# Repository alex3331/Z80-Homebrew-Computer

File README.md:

# Z80-Homebrew-Computer
Custom-built Z80 computer with video display, PS/2 keyboard, sound, and ROM monitor

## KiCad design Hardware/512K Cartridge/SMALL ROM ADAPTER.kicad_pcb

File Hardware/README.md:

Z80 computer hardware schematics and PCB designs.

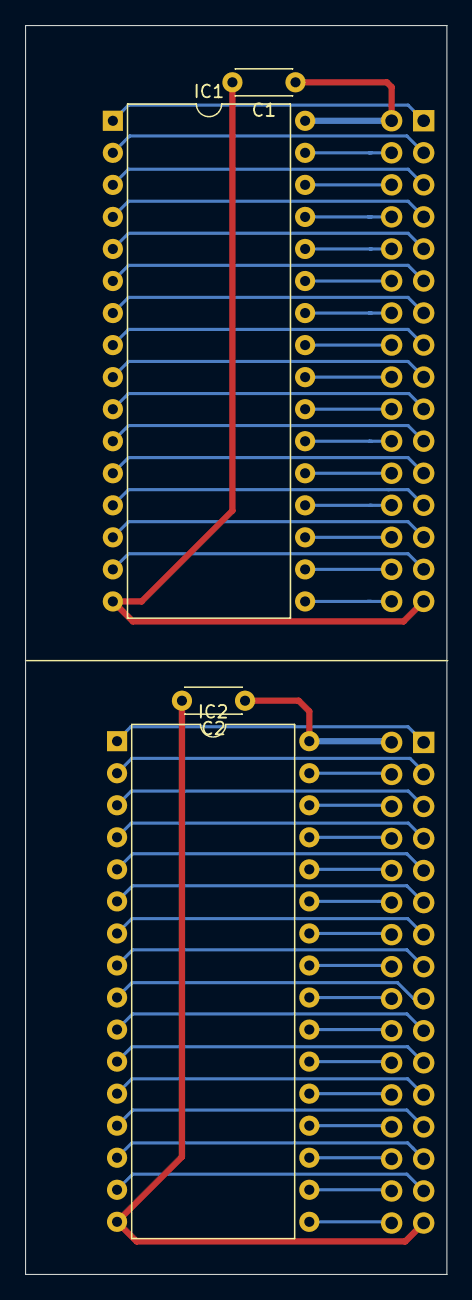
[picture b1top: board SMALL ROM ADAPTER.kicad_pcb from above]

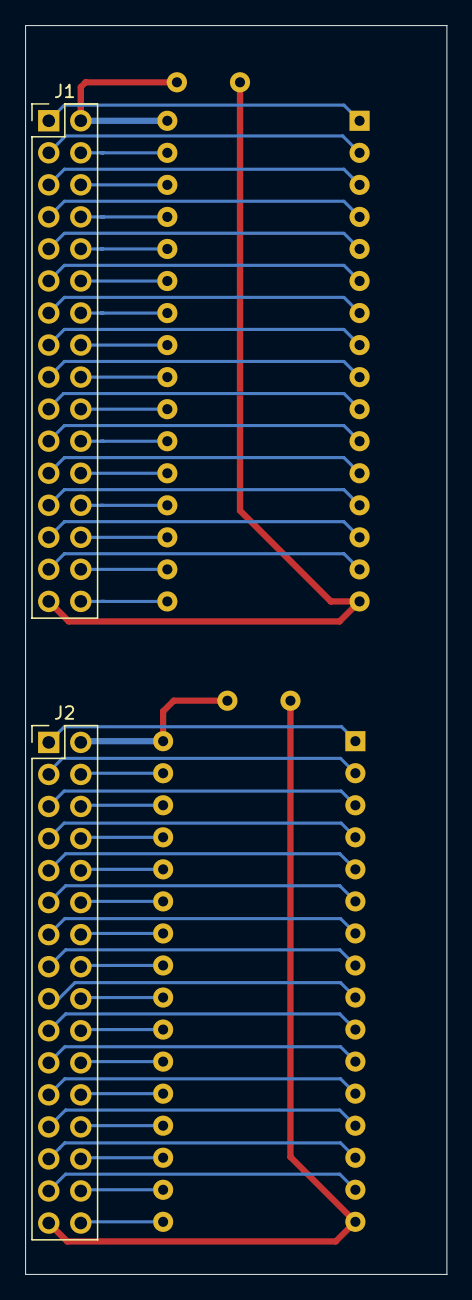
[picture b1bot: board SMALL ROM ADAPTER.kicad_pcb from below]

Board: 2 copper layers, 33.4 x 99.0 mm, 6 parts (2 on the bottom side), 64 nets.

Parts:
C1, C2: 0.1 uF; C_Disc_D4.3mm_W1.9mm_P5.00mm
IC1, IC2: SST39SF040-70-4C-PHE; DIP-32_W15.24mm
J1, J2: Conn_02x16_Odd_Even; PinHeader_2x16_P2.54mm_Vertical

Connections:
/1: IC1.1, J1.1
/1a: IC2.1, J2.1
/2: C1.1, IC1.32, J1.2
/2a: C2.1, IC2.32, J2.2
/3: IC1.2, J1.3
/3a: IC2.2, J2.3
/4: IC1.31, J1.4
/4a: IC2.31, J2.4
/5: IC1.3, J1.5
/5a: IC2.3, J2.5
/6: IC1.30, J1.6
/6a: IC2.30, J2.6
/7: IC1.4, J1.7
/7a: IC2.4, J2.7
/8: IC1.29, J1.8
/8a: IC2.29, J2.8
/9: IC1.5, J1.9
/9a: IC2.5, J2.9
/10: IC1.28, J1.10
/10a: IC2.28, J2.10
/11: IC1.6, J1.11
/11a: IC2.6, J2.11
/12: IC1.27, J1.12
/12a: IC2.27, J2.12
/13: IC1.7, J1.13
/13a: IC2.7, J2.13
/14: IC1.26, J1.14
/14a: IC2.26, J2.14
/15: IC1.8, J1.15
/15a: IC2.8, J2.15
/16: IC1.25, J1.16
/16a: IC2.25, J2.16
/17: IC1.9, J1.17
/17a: IC2.9, J2.17
/18: IC1.24, J1.18
/18a: IC2.24, J2.18
/19: IC1.10, J1.19
/19a: IC2.10, J2.19
/20: IC1.23, J1.20
/20a: IC2.23, J2.20
/21: IC1.11, J1.21
/21a: IC2.11, J2.21
/22: IC1.22, J1.22
/22a: IC2.22, J2.22
/23: IC1.12, J1.23
/23a: IC2.12, J2.23
/24: IC1.21, J1.24
/24a: IC2.21, J2.24
/25: IC1.13, J1.25
/25a: IC2.13, J2.25
/26: IC1.20, J1.26
/26a: IC2.20, J2.26
/27: IC1.14, J1.27
/27a: IC2.14, J2.27
/28: IC1.19, J1.28
/28a: IC2.19, J2.28
/29: IC1.15, J1.29
/29a: IC2.15, J2.29
/30: IC1.18, J1.30
/30a: IC2.18, J2.30
/31: C1.2, IC1.16, J1.31
/31a: C2.2, IC2.16, J2.31
/32: IC1.17, J1.32
/32a: IC2.17, J2.32

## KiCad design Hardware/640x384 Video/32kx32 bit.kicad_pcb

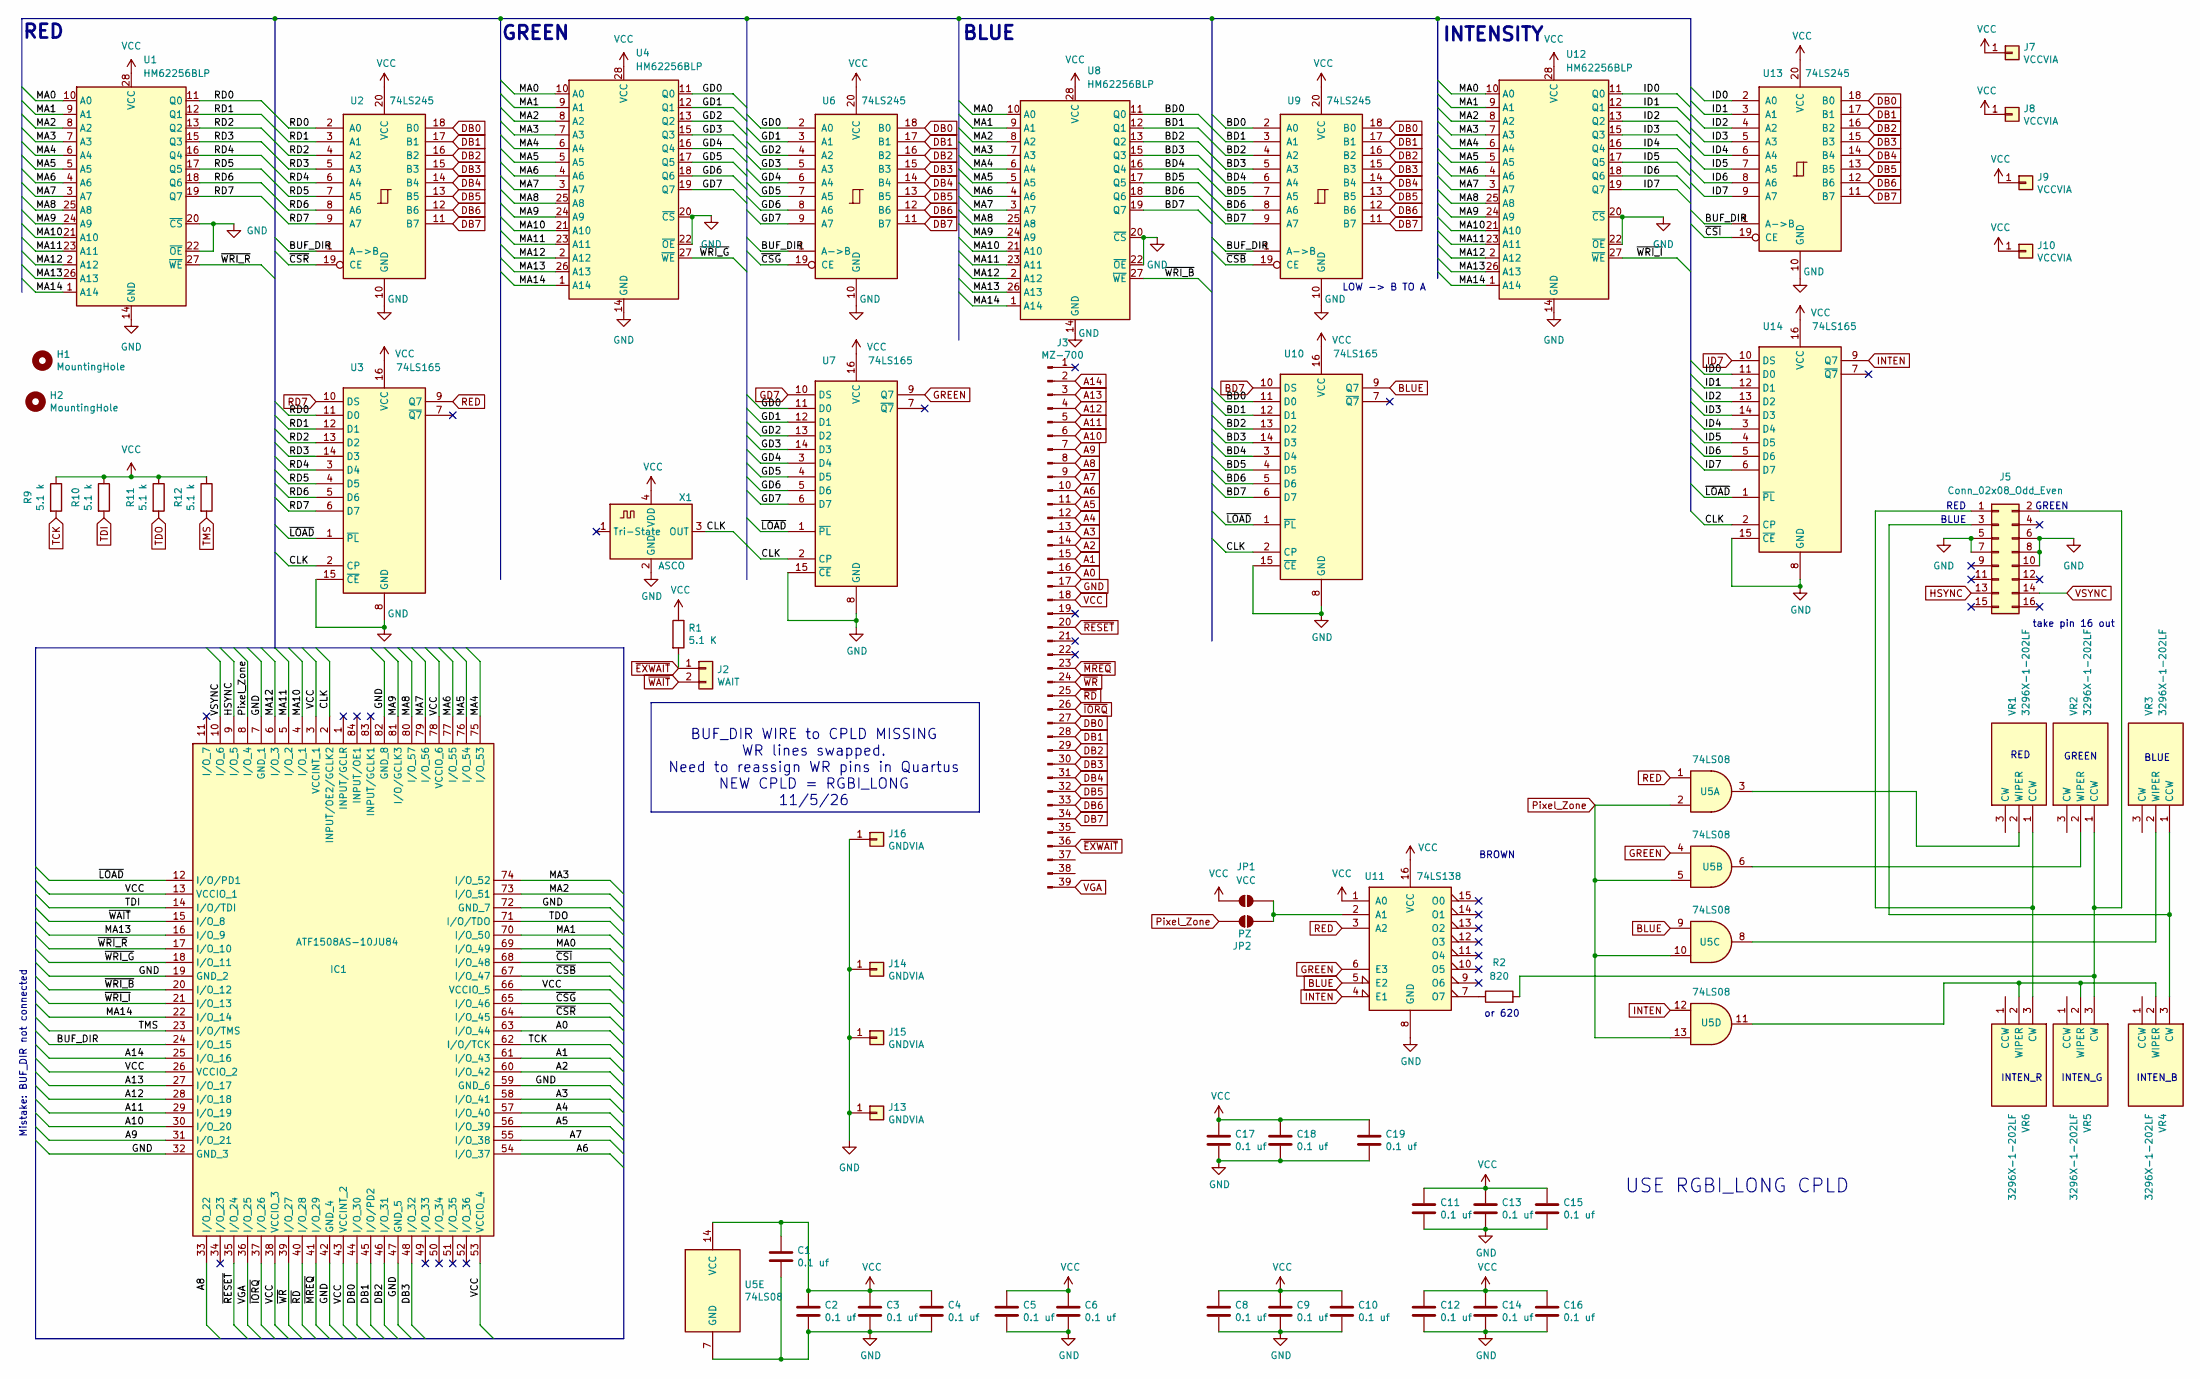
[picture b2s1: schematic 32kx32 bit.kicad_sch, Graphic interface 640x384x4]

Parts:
C1, C2, C3, C4, C5, C6, C8, C9, C10, C11, C12, C13, C14, C15, C16: 0.1 uf; C_Disc_D4.3mm_W1.9mm_P5.00mm
C17, C18, C19: 0.1 uf; C_Disc_D3.0mm_W2.0mm_P2.50mm
H1, H2: MountingHole; MountingHole_3.2mm_M3
IC1: ATF1508AS-10JU84; PLCC-84_THT-Socket; Manufacturer_Part_Number ATF1508AS-10JU84; Mouser Part Number 556-ATF1508AS-10JU84
J2: WAIT; PinHeader_1x02_P2.54mm_Vertical
J3: MZ-700; PinHeader_1x39_P2.54mm_Vertical
J5: Conn_02x08_Odd_Even; PinHeader_2x08_P2.54mm_Vertical
J7, J8, J9, J10: VCCVIA; PinHeader_1x01_P2.54mm_Vertical
J13, J14, J15, J16: GNDVIA; PinHeader_1x01_P2.54mm_Vertical
JP1: VCC; SolderJumper-2_P1.3mm_Open_RoundedPad1.0x1.5mm
JP2: PZ; SolderJumper-2_P1.3mm_Open_RoundedPad1.0x1.5mm
R1: 5.1 K; R_Axial_DIN0204_L3.6mm_D1.6mm_P5.08mm_Horizontal
R2: 820; R_Axial_DIN0204_L3.6mm_D1.6mm_P5.08mm_Horizontal
R9, R10, R11, R12: 5.1 k; R_Axial_DIN0204_L3.6mm_D1.6mm_P5.08mm_Horizontal
U1, U4, U8, U12: HM62256BLP; DIP-28_W7.62mm
U2, U6, U9, U13: 74LS245; DIP-20_W7.62mm
U3, U7, U10, U14: 74LS165; DIP-16_W7.62mm
U5: 74LS08; DIP-14_W7.62mm
U11: 74LS138; DIP-16_W7.62mm
VR1, VR2, VR3, VR4, VR5, VR6: 3296X-1-202LF; 3296X1202LF; Manufacturer_Part_Number 3296X-1-202LF; Mouser Part Number 652-3296X-1-202LF
X1: ASCO; Oscillator_DIP-8

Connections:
/BD0: U8.11 (Q0), U9.2 (A0), U10.11 (D0)
/BD1: U8.12 (Q1), U9.3 (A1), U10.12 (D1)
/BD2: U8.13 (Q2), U9.4 (A2), U10.13 (D2)
/BD3: U8.15 (Q3), U9.5 (A3), U10.14 (D3)
/BD4: U8.16 (Q4), U9.6 (A4), U10.3 (D4)
/BD5: U8.17 (Q5), U9.7 (A5), U10.4 (D5)
/BD6: U8.18 (Q6), U9.8 (A6), U10.5 (D6)
/BUF_DIR: IC1.24 (I/O_15), U2.1 (A->B), U6.1 (A->B), U9.1 (A->B), U13.1 (A->B)
/CLK: IC1.2 (INPUT/OE2/GCLK2), U3.2 (CP), U7.2 (CP), U10.2 (CP), U14.2 (CP), X1.3 (OUT)
/GD0: U4.11 (Q0), U6.2 (A0), U7.11 (D0)
/GD1: U4.12 (Q1), U6.3 (A1), U7.12 (D1)
/GD2: U4.13 (Q2), U6.4 (A2), U7.13 (D2)
/GD3: U4.15 (Q3), U6.5 (A3), U7.14 (D3)
/GD4: U4.16 (Q4), U6.6 (A4), U7.3 (D4)
/GD5: U4.17 (Q5), U6.7 (A5), U7.4 (D5)
/GD6: U4.18 (Q6), U6.8 (A6), U7.5 (D6)
/ID0: U12.11 (Q0), U13.2 (A0), U14.11 (D0)
/ID1: U12.12 (Q1), U13.3 (A1), U14.12 (D1)
/ID2: U12.13 (Q2), U13.4 (A2), U14.13 (D2)
/ID3: U12.15 (Q3), U13.5 (A3), U14.14 (D3)
/ID4: U12.16 (Q4), U13.6 (A4), U14.3 (D4)
/ID5: U12.17 (Q5), U13.7 (A5), U14.4 (D5)
/ID6: U12.18 (Q6), U13.8 (A6), U14.5 (D6)
/MA0: IC1.69 (I/O_49), U1.10 (A0), U4.10 (A0), U8.10 (A0), U12.10 (A0)
/MA1: IC1.70 (I/O_50), U1.9 (A1), U4.9 (A1), U8.9 (A1), U12.9 (A1)
/MA2: IC1.73 (I/O_51), U1.8 (A2), U4.8 (A2), U8.8 (A2), U12.8 (A2)
/MA3: IC1.74 (I/O_52), U1.7 (A3), U4.7 (A3), U8.7 (A3), U12.7 (A3)
/MA4: IC1.75 (I/O_53), U1.6 (A4), U4.6 (A4), U8.6 (A4), U12.6 (A4)
/MA5: IC1.76 (I/O_54), U1.5 (A5), U4.5 (A5), U8.5 (A5), U12.5 (A5)
/MA6: IC1.77 (I/O_55), U1.4 (A6), U4.4 (A6), U8.4 (A6), U12.4 (A6)
/MA7: IC1.79 (I/O_56), U1.3 (A7), U4.3 (A7), U8.3 (A7), U12.3 (A7)
/MA8: IC1.80 (I/O_57), U1.25 (A8), U4.25 (A8), U8.25 (A8), U12.25 (A8)
/MA9: IC1.81 (I/O/GCLK3), U1.24 (A9), U4.24 (A9), U8.24 (A9), U12.24 (A9)
/MA10: IC1.4 (I/O_1), U1.21 (A10), U4.21 (A10), U8.21 (A10), U12.21 (A10)
/MA11: IC1.5 (I/O_2), U1.23 (A11), U4.23 (A11), U8.23 (A11), U12.23 (A11)
/MA12: IC1.6 (I/O_3), U1.2 (A12), U4.2 (A12), U8.2 (A12), U12.2 (A12)
/MA13: IC1.16 (I/O_9), U1.26 (A13), U4.26 (A13), U8.26 (A13), U12.26 (A13)
/MA14: IC1.22 (I/O_14), U1.1 (A14), U4.1 (A14), U8.1 (A14), U12.1 (A14)
/RD0: U1.11 (Q0), U2.2 (A0), U3.11 (D0)
/RD1: U1.12 (Q1), U2.3 (A1), U3.12 (D1)
/RD2: U1.13 (Q2), U2.4 (A2), U3.13 (D2)
/RD3: U1.15 (Q3), U2.5 (A3), U3.14 (D3)
/RD4: U1.16 (Q4), U2.6 (A4), U3.3 (D4)
/RD5: U1.17 (Q5), U2.7 (A5), U3.4 (D5)
/RD6: U1.18 (Q6), U2.8 (A6), U3.5 (D6)
/~CSB: IC1.67 (I/O_47), U9.19 (CE)
/~CSG: IC1.65 (I/O_46), U6.19 (CE)
/~CSI: IC1.68 (I/O_48), U13.19 (CE)
/~CSR: IC1.64 (I/O_45), U2.19 (CE)
/~LOAD: IC1.12 (I/O/PD1), U3.1 (~PL), U7.1 (~PL), U10.1 (~PL), U14.1 (~PL)
/~WRI_B: IC1.20 (I/O_12), U8.27 (~WE)
/~WRI_G: IC1.18 (I/O_11), U4.27 (~WE)
/~WRI_I: IC1.21 (I/O_13), U12.27 (~WE)
/~WRI_R: IC1.17 (I/O_10), U1.27 (~WE)
A0: IC1.63 (I/O_44), J3.16
A1: IC1.61 (I/O_43), J3.15
A2: IC1.60 (I/O_42), J3.14
A3: IC1.58 (I/O_41), J3.13
A4: IC1.57 (I/O_40), J3.12
A5: IC1.56 (I/O_39), J3.11
A6: IC1.54 (I/O_37), J3.10
A7: IC1.55 (I/O_38), J3.9
A8: IC1.33 (I/O_22), J3.8
A9: IC1.31 (I/O_21), J3.7
A10: IC1.30 (I/O_20), J3.6
A11: IC1.29 (I/O_19), J3.5
A12: IC1.28 (I/O_18), J3.4
A13: IC1.27 (I/O_17), J3.3
A14: IC1.25 (I/O_16), J3.2
BD7: U8.19 (Q7), U9.9 (A7), U10.6 (D7), U10.10 (DS)
BLUE: U5.9, U10.9 (Q7), U11.5 (E2)
DB0: IC1.44 (I/O_30), J3.27, U2.18 (B0), U6.18 (B0), U9.18 (B0), U13.18 (B0)
DB1: IC1.45 (I/O/PD2), J3.28, U2.17 (B1), U6.17 (B1), U9.17 (B1), U13.17 (B1)
DB2: IC1.46 (I/O_31), J3.29, U2.16 (B2), U6.16 (B2), U9.16 (B2), U13.16 (B2)
DB3: IC1.48 (I/O_32), J3.30, U2.15 (B3), U6.15 (B3), U9.15 (B3), U13.15 (B3)
DB4: J3.31, U2.14 (B4), U6.14 (B4), U9.14 (B4), U13.14 (B4)
DB5: J3.32, U2.13 (B5), U6.13 (B5), U9.13 (B5), U13.13 (B5)
DB6: J3.33, U2.12 (B6), U6.12 (B6), U9.12 (B6), U13.12 (B6)
DB7: J3.34, U2.11 (B7), U6.11 (B7), U9.11 (B7), U13.11 (B7)
GD7: U4.19 (Q7), U6.9 (A7), U7.6 (D7), U7.10 (DS)
GND: C1.2, C2.2, C3.2, C4.2, C5.2, C6.2, C8.2, C9.2, C10.2, C11.2, C12.2, C13.2, C14.2, C15.2, C16.2, C17.2, C18.2, C19.2, IC1.7 (GND_1), IC1.19 (GND_2), IC1.32 (GND_3), IC1.42 (GND_4), IC1.47 (GND_5), IC1.59 (GND_6), IC1.72 (GND_7), IC1.82 (GND_8), J3.17, J5.5, J5.6, J5.7, J5.8, J5.10, J13.1 (Pin_1_1), J14.1 (Pin_1_1), J15.1 (Pin_1_1), J16.1 (Pin_1_1), U1.14 (GND), U1.20 (~CS), U1.22 (~OE), U2.10 (GND), U3.8 (GND), U3.15 (~CE), U4.14 (GND), U4.20 (~CS), U4.22 (~OE), U5.7 (GND), U6.10 (GND), U7.8 (GND), U7.15 (~CE), U8.14 (GND), U8.20 (~CS), U8.22 (~OE), U9.10 (GND), U10.8 (GND), U10.15 (~CE), U11.8 (GND), U12.14 (GND), U12.20 (~CS), U12.22 (~OE), U13.10 (GND), U14.8 (GND), U14.15 (~CE), X1.2 (GND)
GREEN: U5.4, U7.9 (Q7), U11.6 (E3)
HSYNC: IC1.9 (I/O_5), J5.13
ID7: U12.19 (Q7), U13.9 (A7), U14.6 (D7), U14.10 (DS)
INTEN: U5.12, U11.4 (E1), U14.9 (Q7)
unnamed: J5.1, VR1.1 (CCW), VR6.3 (CW)
unnamed: J5.2, R2.2, VR2.1 (CCW), VR5.3 (CW)
unnamed: J5.3, VR3.1 (CCW), VR4.3 (CW)
unnamed: JP1.2 (B), JP2.2 (B), U11.2 (A1)
unnamed: R2.1, U11.7 (O7)
unnamed: U5.3, VR1.2 (WIPER)
unnamed: U5.6, VR2.2 (WIPER)
unnamed: U5.8, VR3.2 (WIPER)
unnamed: U5.11, VR4.2 (WIPER), VR5.2 (WIPER), VR6.2 (WIPER)
Pixel_Zone: IC1.8 (I/O_4), JP2.1 (A), U5.2, U5.5, U5.10, U5.13
RD7: U1.19 (Q7), U2.9 (A7), U3.6 (D7), U3.10 (DS)
RED: U3.9 (Q7), U5.1, U11.3 (A2)
TCK: IC1.62 (I/O/TCK), R9.2
TDI: IC1.14 (I/O/TDI), R10.2
TDO: IC1.71 (I/O/TDO), R11.2
TMS: IC1.23 (I/O/TMS), R12.2
VCC: C1.1, C2.1, C3.1, C4.1, C5.1, C6.1, C8.1, C9.1, C10.1, C11.1, C12.1, C13.1, C14.1, C15.1, C16.1, C17.1, C18.1, C19.1, IC1.3 (VCCINT_1), IC1.13 (VCCIO_1), IC1.26 (VCCIO_2), IC1.38 (VCCIO_3), IC1.43 (VCCINT_2), IC1.53 (VCCIO_4), IC1.66 (VCCIO_5), IC1.78 (VCCIO_6), J3.18, J7.1 (Pin_1_1), J8.1 (Pin_1_1), J9.1 (Pin_1_1), J10.1 (Pin_1_1), JP1.1 (A), R1.1, R9.1, R10.1, R11.1, R12.1, U1.28 (VCC), U2.20 (VCC), U3.16 (VCC), U4.28 (VCC), U5.14 (VCC), U6.20 (VCC), U7.16 (VCC), U8.28 (VCC), U9.20 (VCC), U10.16 (VCC), U11.1 (A0), U11.16 (VCC), U12.28 (VCC), U13.20 (VCC), U14.16 (VCC), X1.4 (VDD)
VGA: IC1.36 (I/O_25), J3.39
VSYNC: IC1.10 (I/O_6), J5.14
~EXWAIT: J2.1, J3.36, R1.2
~IORQ: IC1.37 (I/O_26), J3.26
~MREQ: IC1.41 (I/O_29), J3.23
~RD: IC1.40 (I/O_28), J3.25
~RESET: IC1.35 (I/O_24), J3.20
~WAIT: IC1.15 (I/O_8), J2.2
~WR: IC1.39 (I/O_27), J3.24

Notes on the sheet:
GREEN
Mistake: BUF_DIR not connected
BLUE
INTEN_G
RED
LOW -> B TO A
INTEN_B
BROWN
USE RGBI_LONG CPLD
or 620
INTENSITY
BUF_DIR WIRE to CPLD MISSING WR lines swapped. Need to reassign WR pins in Quartus NEW CPLD = RGBI_LONG 11/5/26
take pin 16 out
INTEN_R

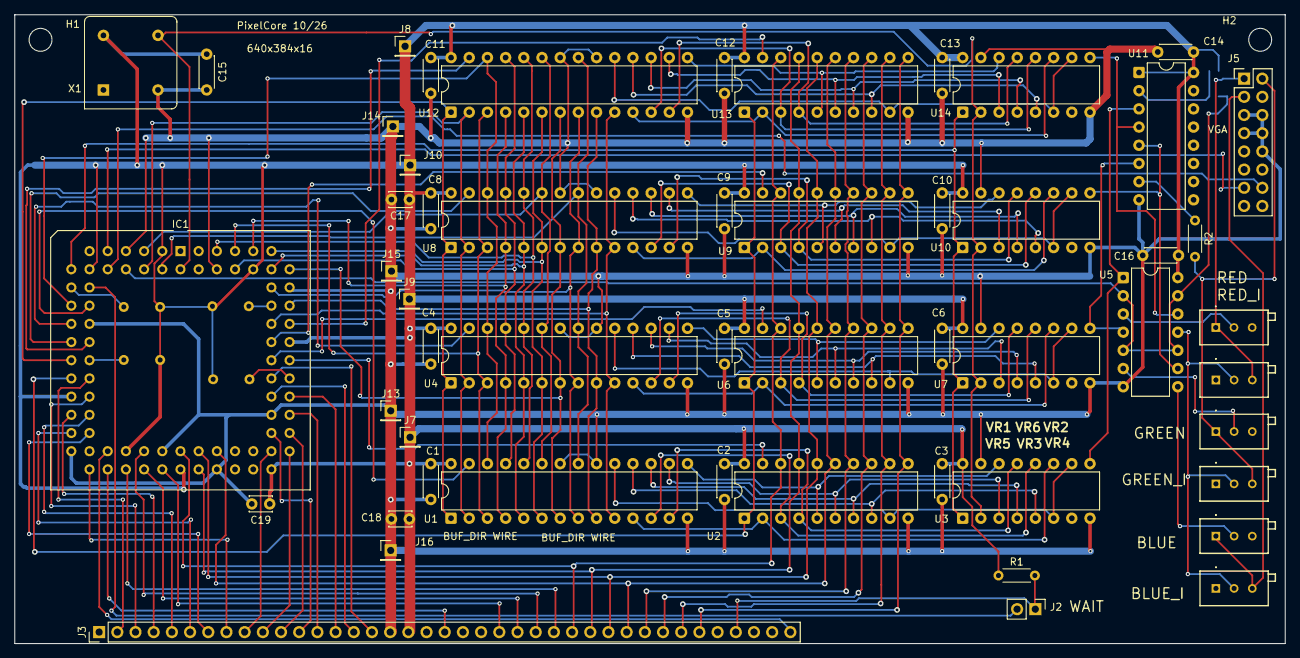
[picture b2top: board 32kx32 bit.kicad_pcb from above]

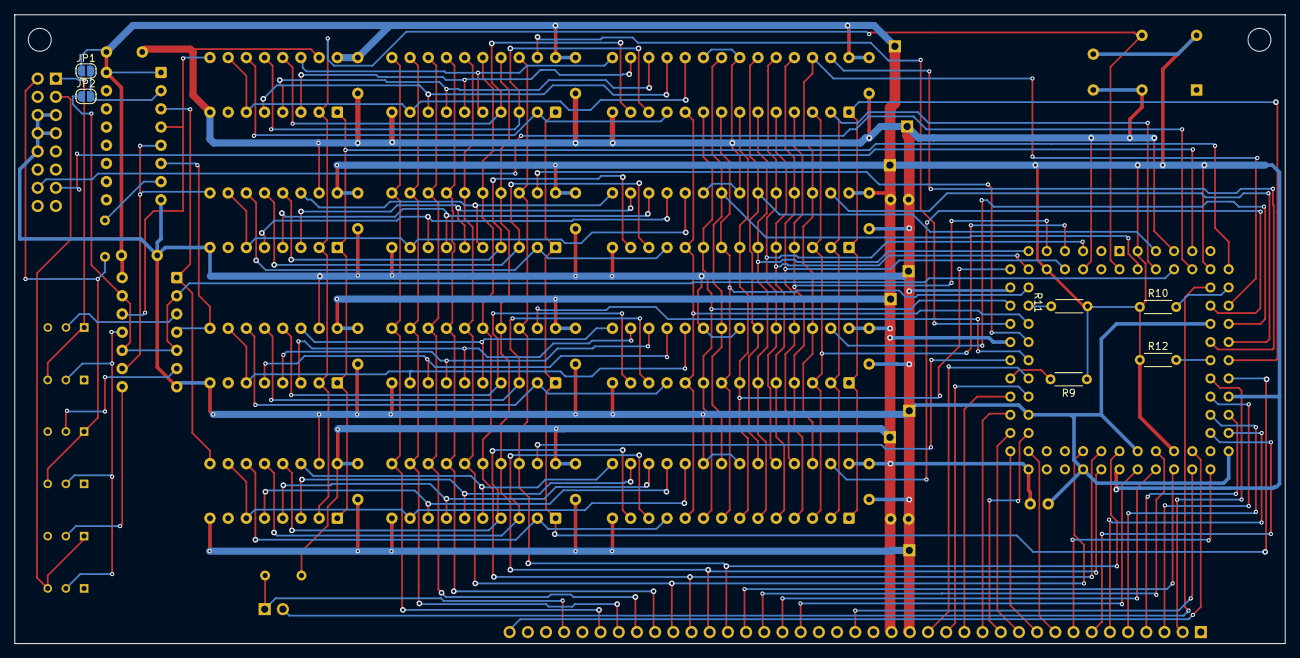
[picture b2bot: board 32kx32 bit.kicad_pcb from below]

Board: 2 copper layers, 177.4 x 87.8 mm, 61 parts (6 on the bottom side), 111 nets.
